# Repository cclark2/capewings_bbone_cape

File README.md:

CapeWings BeagleBone Cape
=========================

Breaks down cape stacks into a form factor easier to debug without having to keep removing capes. Supports selectively jumpering signals between the BeagleBone and up to three capes. Also allows multiple BeagleBones to be connected together. It's a cape developer's dream!

Special thanks to <a href="http://www.sparkfun.com/">SparkFun</a> for use of their open-source EAGLE libraries.

## Project Links
- <a href="http://www.hitchhikeree.org/beaglebone_capes/capewings/">HitchhikerEE page</a>
- <a href="http://www.youtube.com/watch?v=Ci1aKsf_dBM">YouTube video</a>
- <a href="https://docs.google.com/folder/d/0B5HjtPsFD8u5NXZ3VUFZem5UdW8/edit">Design files on Google Drive</a>
- <a href="http://beagleboard.org/CapeContest/entries/CapeWings/">BeagleBone Cape Contest page</a>

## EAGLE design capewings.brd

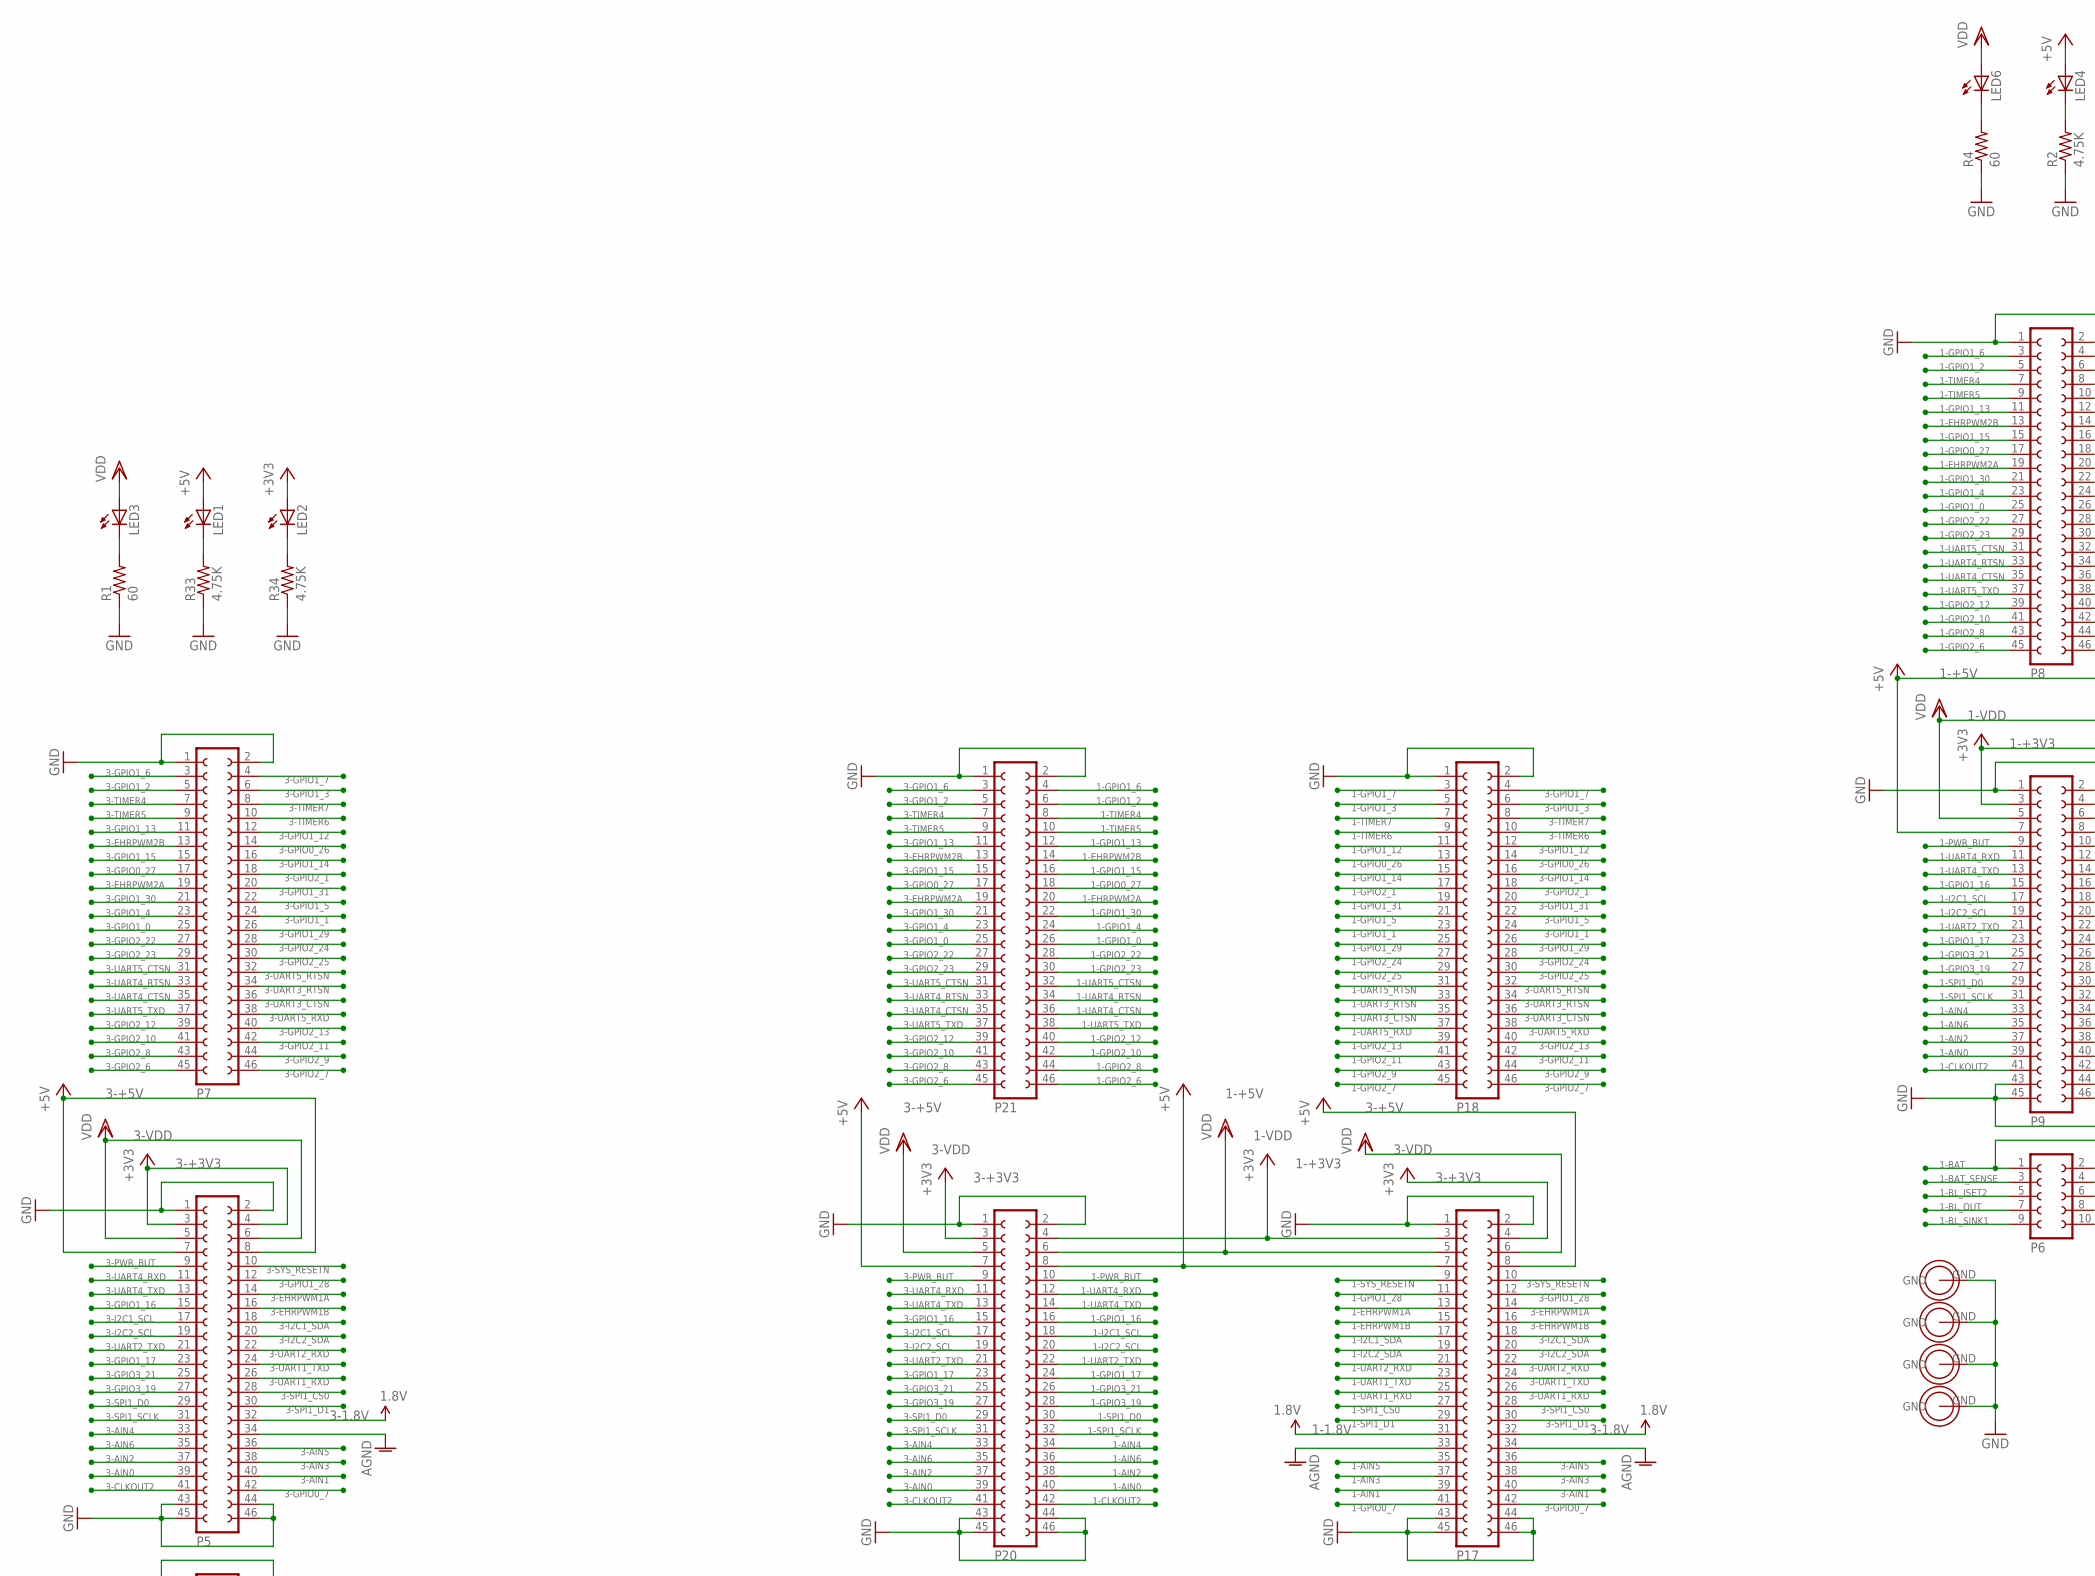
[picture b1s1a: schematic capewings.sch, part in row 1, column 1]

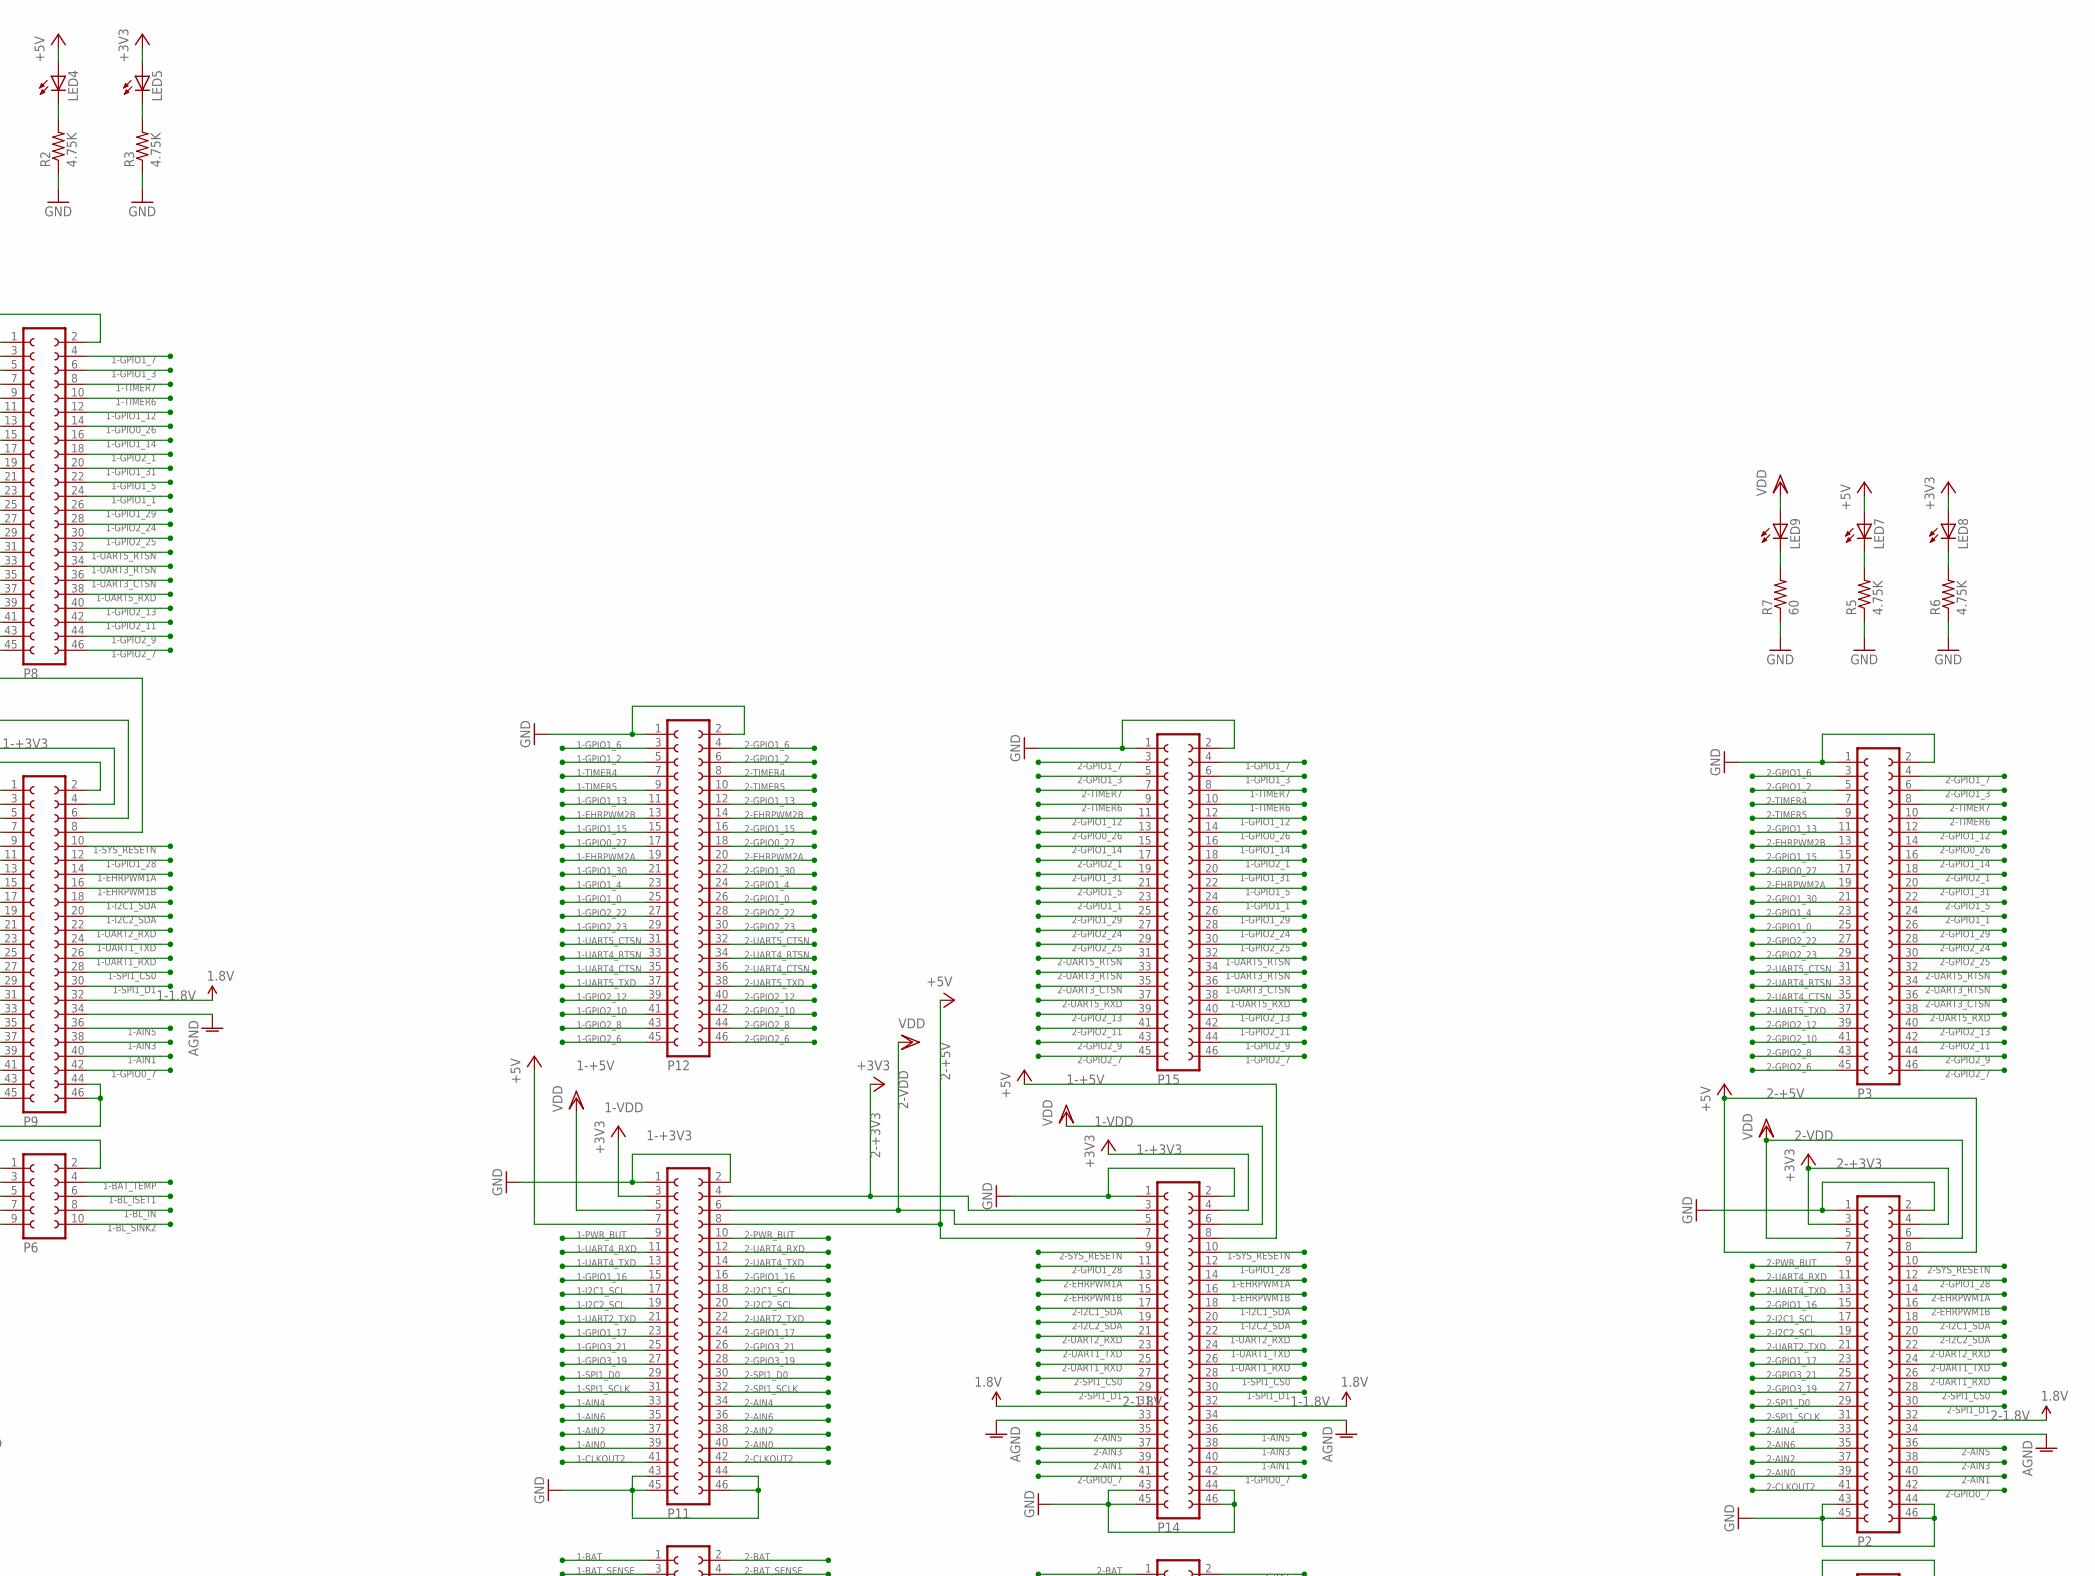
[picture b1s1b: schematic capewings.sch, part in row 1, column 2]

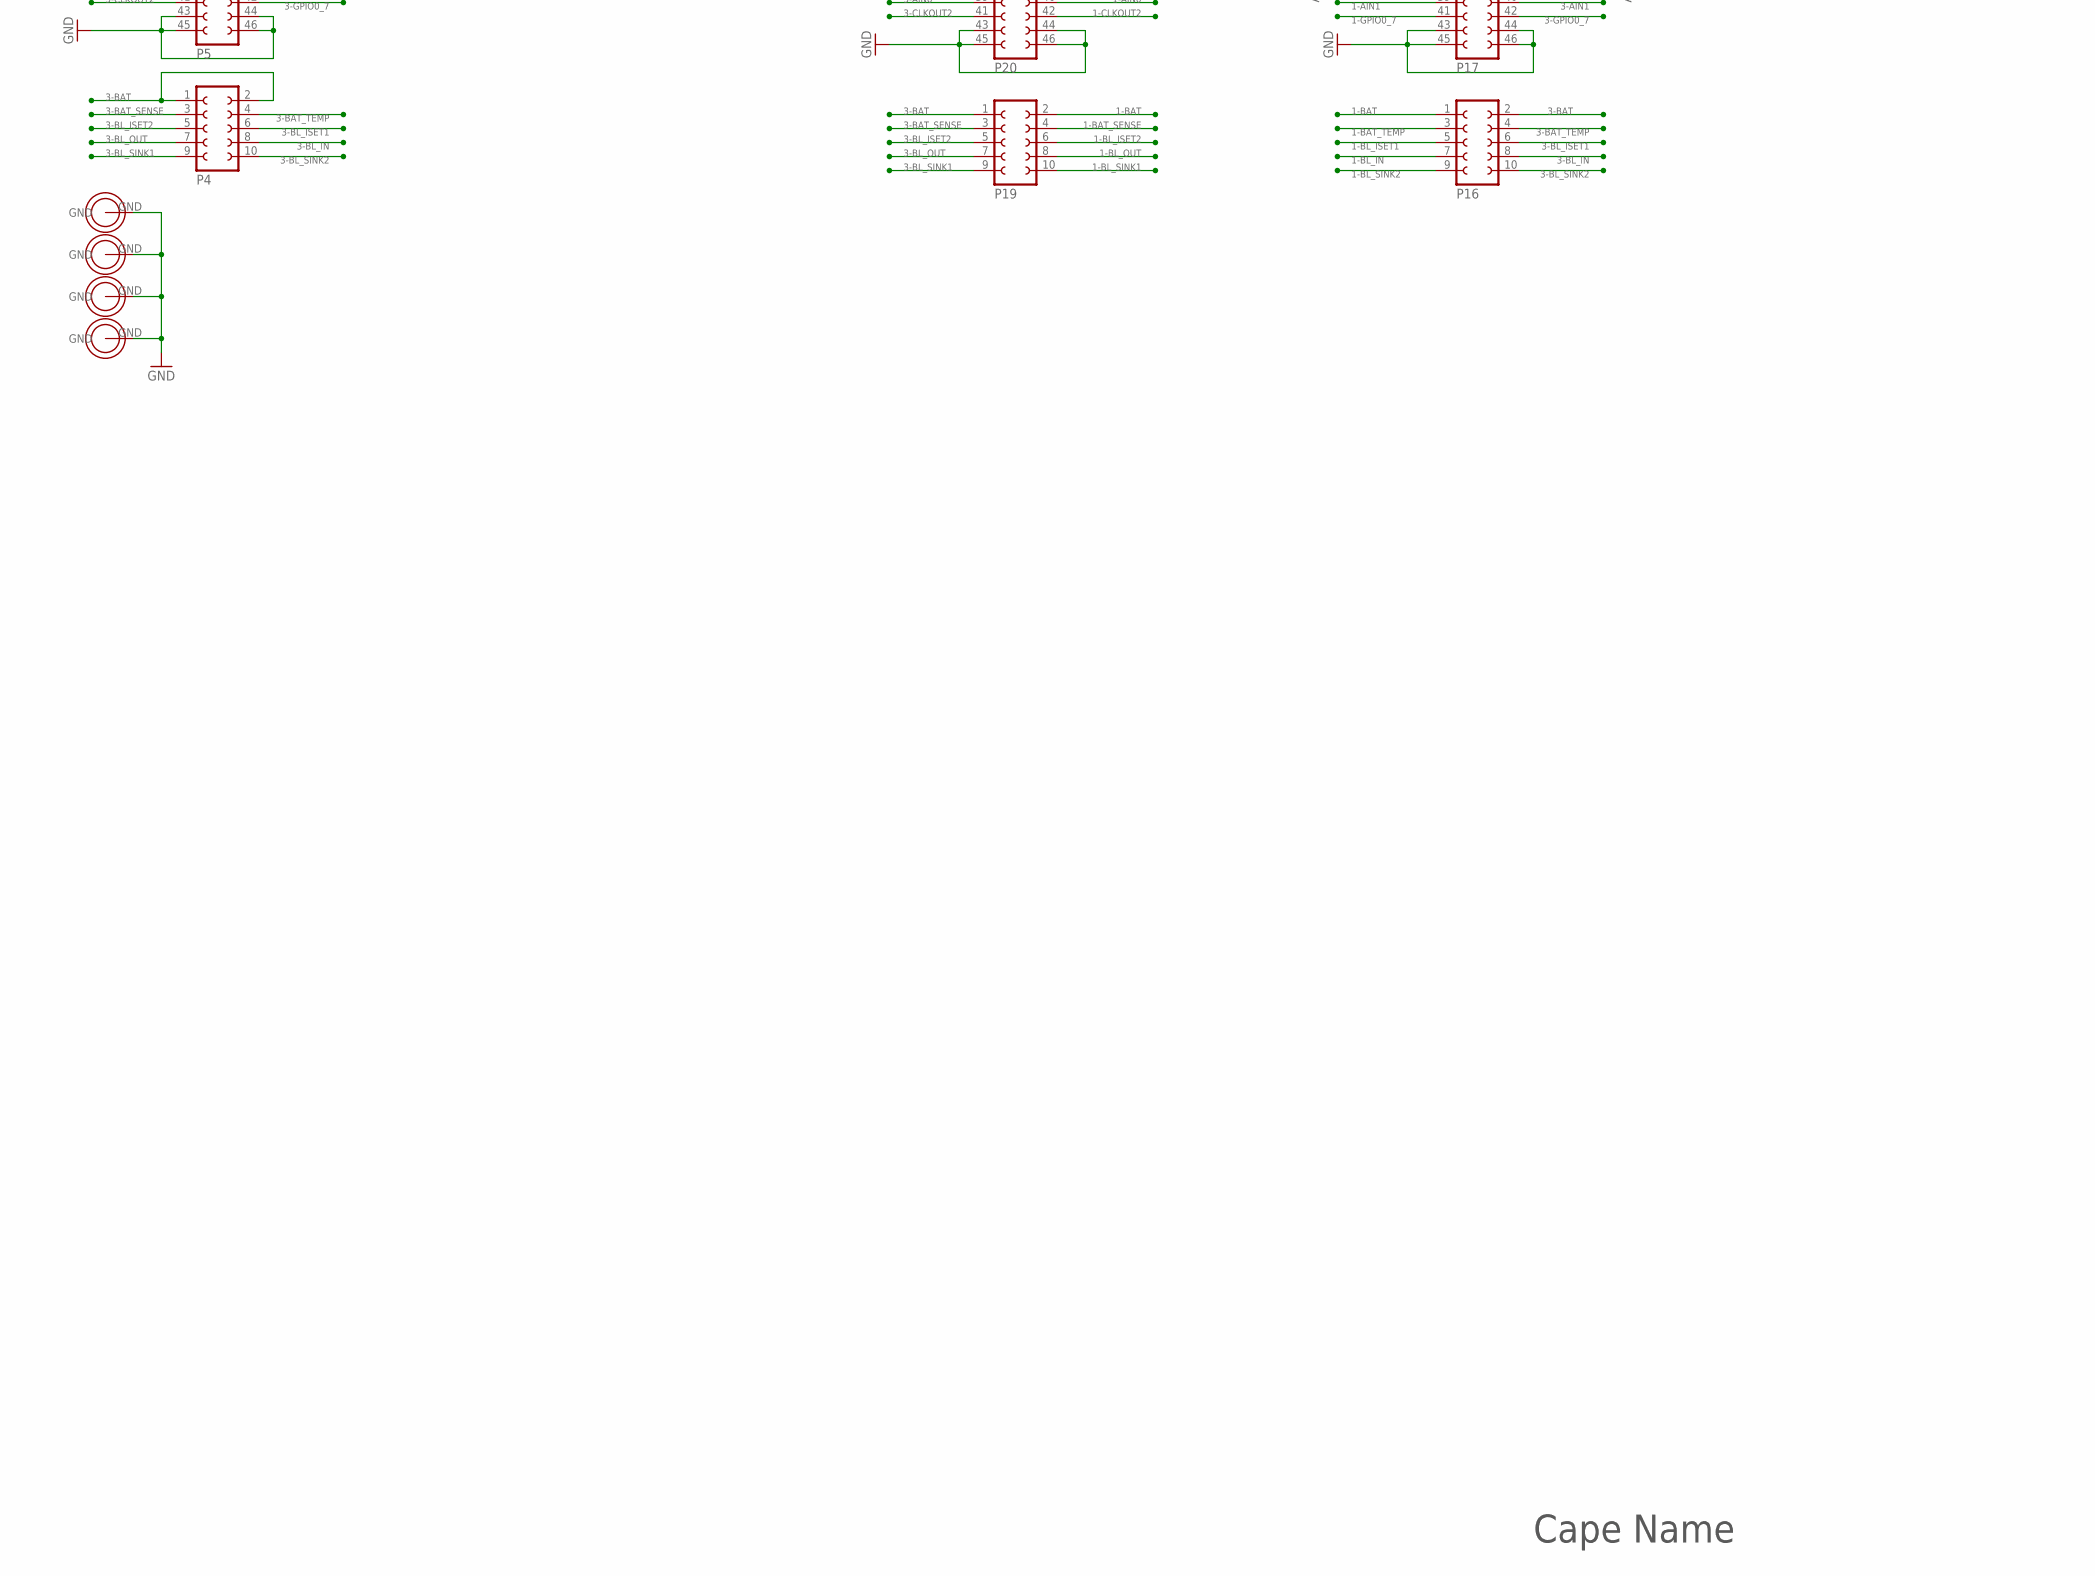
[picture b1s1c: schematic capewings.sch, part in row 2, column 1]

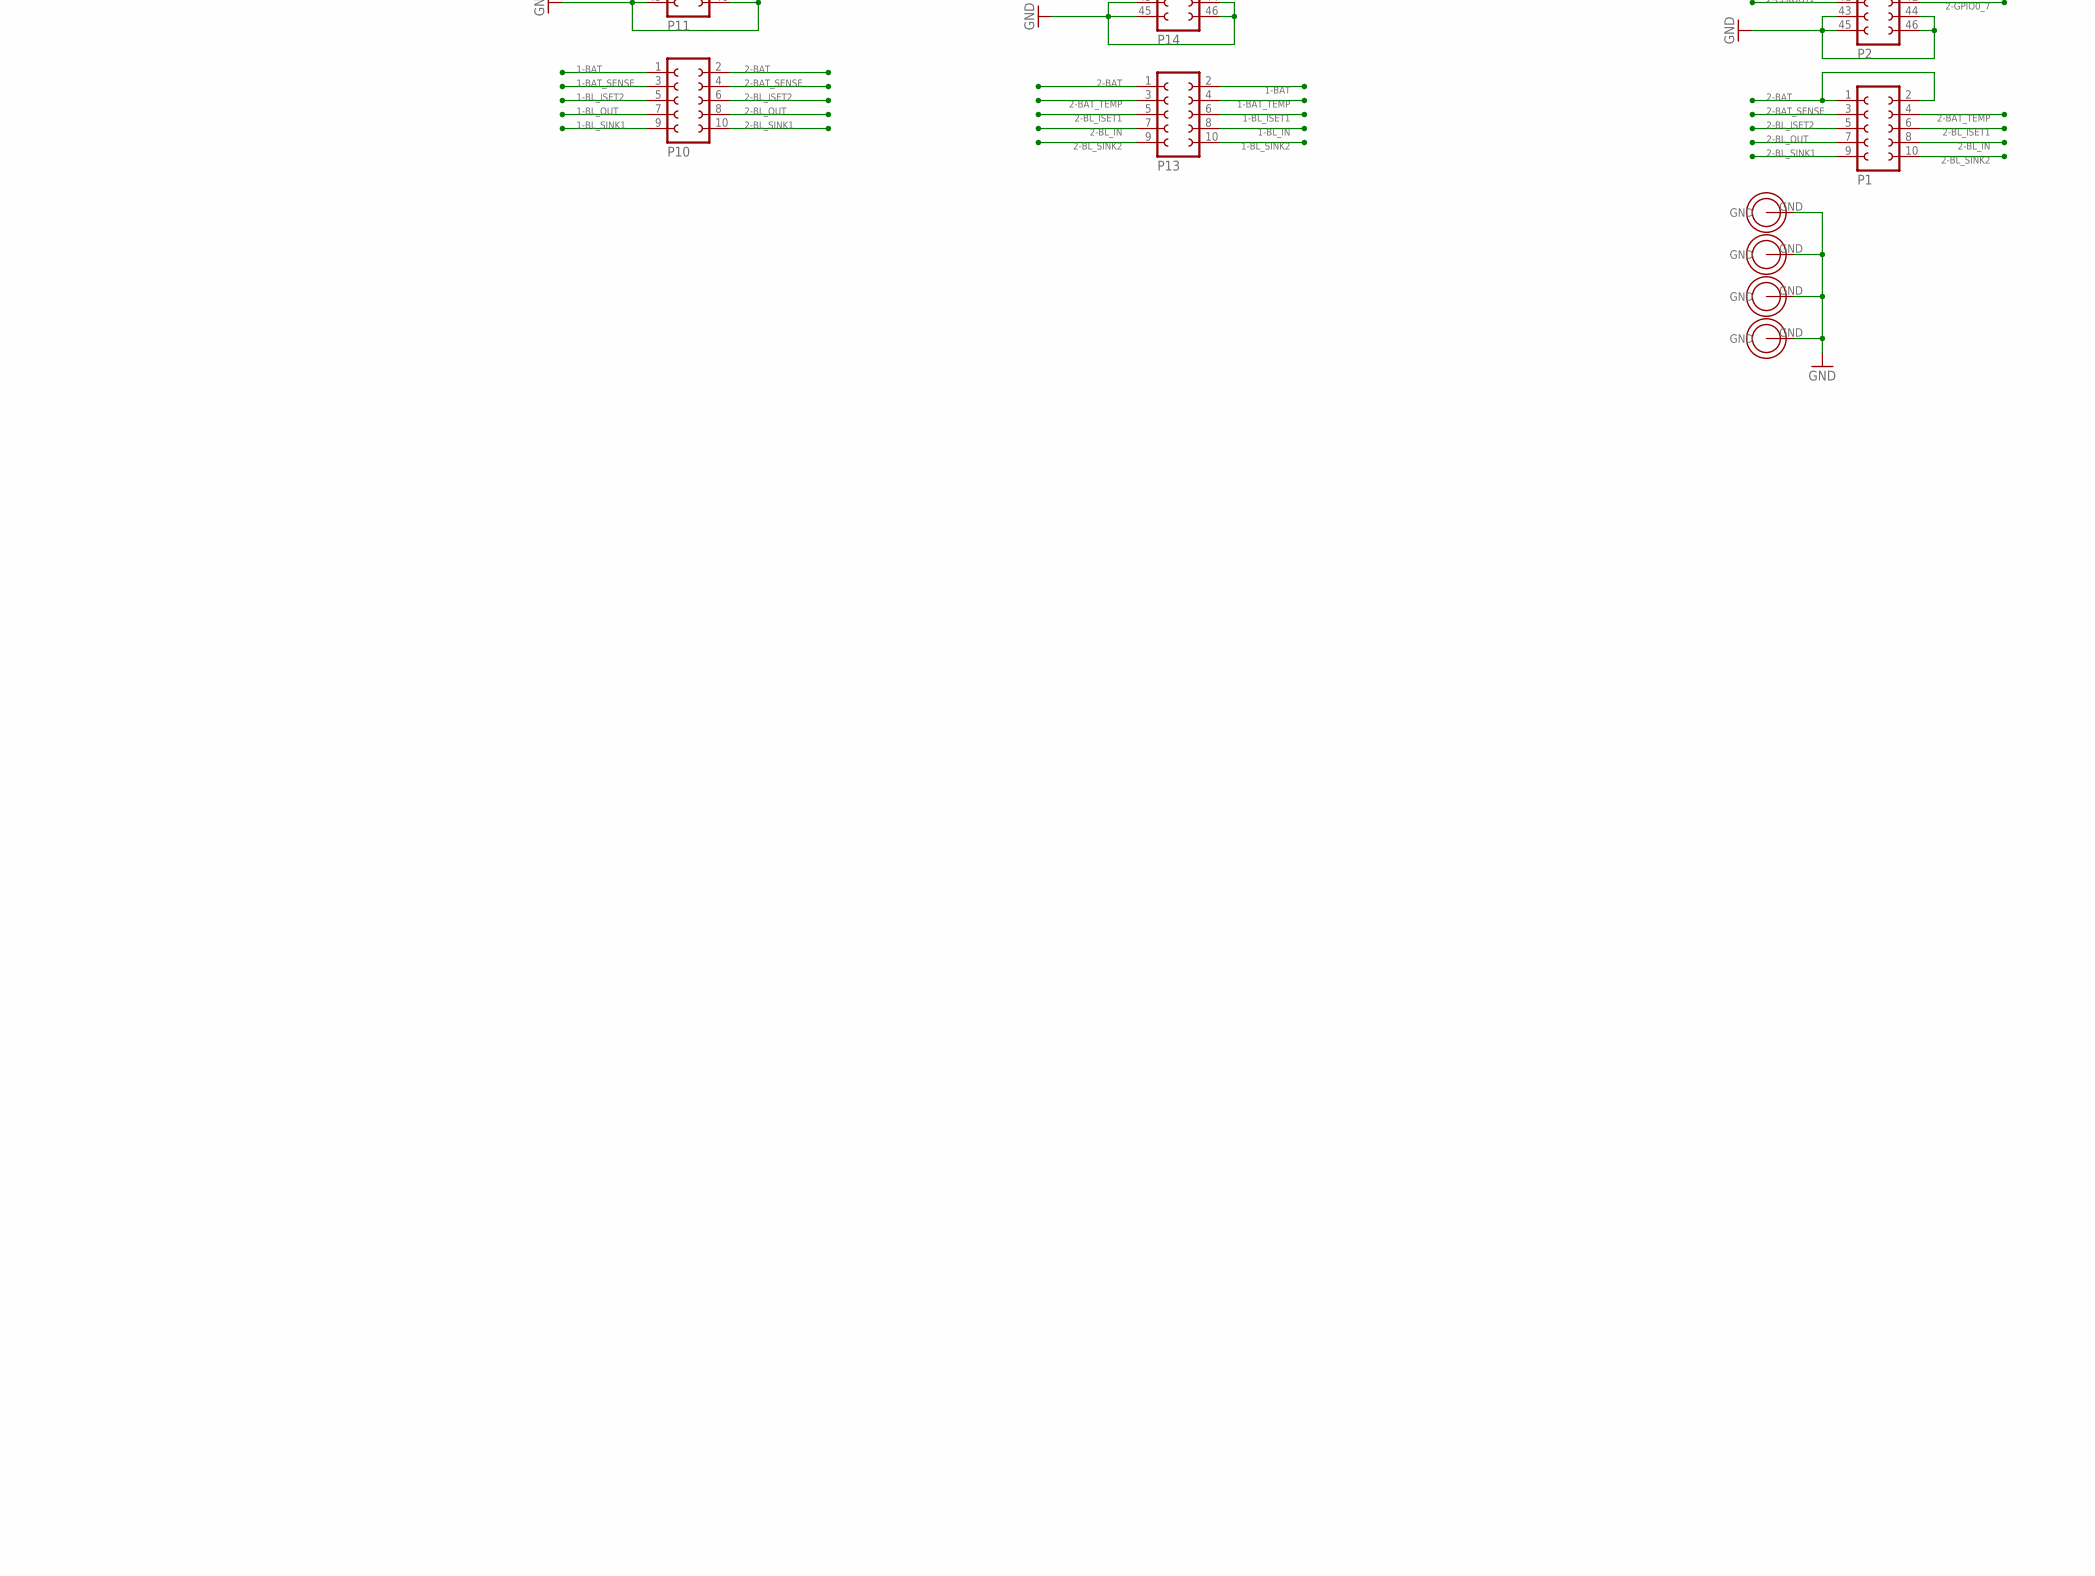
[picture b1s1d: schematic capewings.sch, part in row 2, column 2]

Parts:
H1, H2, H3, H4, H5, H6, H7, H8, H9, H10, H11, H12: HOLE
LED1, LED2, LED3, LED4, LED5, LED6, LED7, LED8, LED9: LEDCHIPLED_0603; CHIPLED_0603
P1, P4, P6, P10, P13, P16, P19: FE05-2
P2, P3, P5, P7, P8, P9, P11, P12, P14, P15, P17, P18, P20, P21: FE23-2
R1, R4: 60; R0603; MPN 302-60.4-RC
R2, R3, R5, R6, R33, R34: 4.75K; R0603
R7: 60; R0603

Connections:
1-1.8V: P9.32, P14.32, P17.31
1-+3V3: LED5.A, P9.3, P9.4, P11.3, P14.4, P17.3, P20.4
1-+5V: LED4.A, P9.7, P9.8, P11.7, P14.8, P17.7, P20.8
1-AIN0: P9.39, P11.39, P20.40
1-AIN1: P9.40, P14.40, P17.39
1-AIN2: P9.37, P11.37, P20.38
1-AIN3: P9.38, P14.38, P17.37
1-AIN4: P9.33, P11.33, P20.34
1-AIN5: P9.36, P14.36, P17.35
1-AIN6: P9.35, P11.35, P20.36
1-BAT: P6.1, P6.2, P10.1, P13.2, P16.1, P19.2
1-BAT_SENSE: P6.3, P10.3, P19.4
1-BAT_TEMP: P6.4, P13.4, P16.3
1-BL_IN: P6.8, P13.8, P16.7
1-BL_ISET1: P6.6, P13.6, P16.5
1-BL_ISET2: P6.5, P10.5, P19.6
1-BL_OUT: P6.7, P10.7, P19.8
1-BL_SINK1: P6.9, P10.9, P19.10
1-BL_SINK2: P6.10, P13.10, P16.9
1-CLKOUT2: P9.41, P11.41, P20.42
1-EHRPWM1A: P9.14, P14.14, P17.13
1-EHRPWM1B: P9.16, P14.16, P17.15
1-EHRPWM2A: P8.19, P12.19, P21.20
1-EHRPWM2B: P8.13, P12.13, P21.14
1-GPIO0_7: P9.42, P14.42, P17.41
1-GPIO0_26: P8.14, P15.14, P18.13
1-GPIO0_27: P8.17, P12.17, P21.18
1-GPIO1_0: P8.25, P12.25, P21.26
1-GPIO1_1: P8.24, P15.24, P18.23
1-GPIO1_2: P8.5, P12.5, P21.6
1-GPIO1_3: P8.6, P15.6, P18.5
1-GPIO1_4: P8.23, P12.23, P21.24
1-GPIO1_5: P8.22, P15.22, P18.21
1-GPIO1_6: P8.3, P12.3, P21.4
1-GPIO1_7: P8.4, P15.4, P18.3
1-GPIO1_12: P8.12, P15.12, P18.11
1-GPIO1_13: P8.11, P12.11, P21.12
1-GPIO1_14: P8.16, P15.16, P18.15
1-GPIO1_15: P8.15, P12.15, P21.16
1-GPIO1_16: P9.15, P11.15, P20.16
1-GPIO1_17: P9.23, P11.23, P20.24
1-GPIO1_28: P9.12, P14.12, P17.11
1-GPIO1_29: P8.26, P15.26, P18.25
1-GPIO1_30: P8.21, P12.21, P21.22
1-GPIO1_31: P8.20, P15.20, P18.19
1-GPIO2_1: P8.18, P15.18, P18.17
1-GPIO2_6: P8.45, P12.45, P21.46
1-GPIO2_7: P8.46, P15.46, P18.45
1-GPIO2_8: P8.43, P12.43, P21.44
1-GPIO2_9: P8.44, P15.44, P18.43
1-GPIO2_10: P8.41, P12.41, P21.42
1-GPIO2_11: P8.42, P15.42, P18.41
1-GPIO2_12: P8.39, P12.39, P21.40
1-GPIO2_13: P8.40, P15.40, P18.39
1-GPIO2_22: P8.27, P12.27, P21.28
1-GPIO2_23: P8.29, P12.29, P21.30
1-GPIO2_24: P8.28, P15.28, P18.27
1-GPIO2_25: P8.30, P15.30, P18.29
1-GPIO3_19: P9.27, P11.27, P20.28
1-GPIO3_21: P9.25, P11.25, P20.26
1-I2C1_SCL: P9.17, P11.17, P20.18
1-I2C1_SDA: P9.18, P14.18, P17.17
1-I2C2_SCL: P9.19, P11.19, P20.20
1-I2C2_SDA: P9.20, P14.20, P17.19
1-PWR_BUT: P9.9, P11.9, P20.10
1-SPI1_CS0: P9.28, P14.28, P17.27
1-SPI1_D0: P9.29, P11.29, P20.30
1-SPI1_D1: P9.30, P14.30, P17.29
1-SPI1_SCLK: P9.31, P11.31, P20.32
1-SYS_RESETN: P9.10, P14.10, P17.9
1-TIMER4: P8.7, P12.7, P21.8
1-TIMER5: P8.9, P12.9, P21.10
1-TIMER6: P8.10, P15.10, P18.9
1-TIMER7: P8.8, P15.8, P18.7
1-UART1_RXD: P9.26, P14.26, P17.25
1-UART1_TXD: P9.24, P14.24, P17.23
1-UART2_RXD: P9.22, P14.22, P17.21
1-UART2_TXD: P9.21, P11.21, P20.22
1-UART3_CTSN: P8.36, P15.36, P18.35
1-UART3_RTSN: P8.34, P15.34, P18.33
1-UART4_CTSN: P8.35, P12.35, P21.36
1-UART4_RTSN: P8.33, P12.33, P21.34
1-UART4_RXD: P9.11, P11.11, P20.12
1-UART4_TXD: P9.13, P11.13, P20.14
1-UART5_CTSN: P8.31, P12.31, P21.32
1-UART5_RTSN: P8.32, P15.32, P18.31
1-UART5_RXD: P8.38, P15.38, P18.37
1-UART5_TXD: P8.37, P12.37, P21.38
1-VDD: LED6.A, P9.5, P9.6, P11.5, P14.6, P17.5, P20.6
2-1.8V: P2.32, P14.31
2-+3V3: LED8.A, P2.3, P2.4, P11.4, P14.3
2-+5V: LED7.A, P2.7, P2.8, P11.8, P14.7
2-AIN0: P2.39, P11.40
2-AIN1: P2.40, P14.39
2-AIN2: P2.37, P11.38
2-AIN3: P2.38, P14.37
2-AIN4: P2.33, P11.34
2-AIN5: P2.36, P14.35
2-AIN6: P2.35, P11.36
2-BAT: P1.1, P1.2, P10.2, P13.1
2-BAT_SENSE: P1.3, P10.4
2-BAT_TEMP: P1.4, P13.3
2-BL_IN: P1.8, P13.7
2-BL_ISET1: P1.6, P13.5
2-BL_ISET2: P1.5, P10.6
2-BL_OUT: P1.7, P10.8
2-BL_SINK1: P1.9, P10.10
2-BL_SINK2: P1.10, P13.9
2-CLKOUT2: P2.41, P11.42
2-EHRPWM1A: P2.14, P14.13
2-EHRPWM1B: P2.16, P14.15
2-EHRPWM2A: P3.19, P12.20
2-EHRPWM2B: P3.13, P12.14
2-GPIO0_7: P2.42, P14.41
2-GPIO0_26: P3.14, P15.13
2-GPIO0_27: P3.17, P12.18
2-GPIO1_0: P3.25, P12.26
2-GPIO1_1: P3.24, P15.23
2-GPIO1_2: P3.5, P12.6
2-GPIO1_3: P3.6, P15.5
2-GPIO1_4: P3.23, P12.24
2-GPIO1_5: P3.22, P15.21
2-GPIO1_6: P3.3, P12.4
2-GPIO1_7: P3.4, P15.3
2-GPIO1_12: P3.12, P15.11
2-GPIO1_13: P3.11, P12.12
2-GPIO1_14: P3.16, P15.15
2-GPIO1_15: P3.15, P12.16
2-GPIO1_16: P2.15, P11.16
2-GPIO1_17: P2.23, P11.24
2-GPIO1_28: P2.12, P14.11
2-GPIO1_29: P3.26, P15.25
2-GPIO1_30: P3.21, P12.22
2-GPIO1_31: P3.20, P15.19
2-GPIO2_1: P3.18, P15.17
2-GPIO2_6: P3.45, P12.46
2-GPIO2_7: P3.46, P15.45
2-GPIO2_8: P3.43, P12.44
2-GPIO2_9: P3.44, P15.43
2-GPIO2_10: P3.41, P12.42
2-GPIO2_11: P3.42, P15.41
2-GPIO2_12: P3.39, P12.40
2-GPIO2_13: P3.40, P15.39
2-GPIO2_22: P3.27, P12.28
2-GPIO2_23: P3.29, P12.30
2-GPIO2_24: P3.28, P15.27
2-GPIO2_25: P3.30, P15.29
2-GPIO3_19: P2.27, P11.28
2-GPIO3_21: P2.25, P11.26
2-I2C1_SCL: P2.17, P11.18
2-I2C1_SDA: P2.18, P14.17
2-I2C2_SCL: P2.19, P11.20
2-I2C2_SDA: P2.20, P14.19
2-PWR_BUT: P2.9, P11.10
2-SPI1_CS0: P2.28, P14.27
2-SPI1_D0: P2.29, P11.30
2-SPI1_D1: P2.30, P14.29
2-SPI1_SCLK: P2.31, P11.32
2-SYS_RESETN: P2.10, P14.9
2-TIMER4: P3.7, P12.8
2-TIMER5: P3.9, P12.10
2-TIMER6: P3.10, P15.9
2-TIMER7: P3.8, P15.7
2-UART1_RXD: P2.26, P14.25
2-UART1_TXD: P2.24, P14.23
2-UART2_RXD: P2.22, P14.21
2-UART2_TXD: P2.21, P11.22
2-UART3_CTSN: P3.36, P15.35
2-UART3_RTSN: P3.34, P15.33
2-UART4_CTSN: P3.35, P12.36
2-UART4_RTSN: P3.33, P12.34
2-UART4_RXD: P2.11, P11.12
2-UART4_TXD: P2.13, P11.14
2-UART5_CTSN: P3.31, P12.32
2-UART5_RTSN: P3.32, P15.31
2-UART5_RXD: P3.38, P15.37
2-UART5_TXD: P3.37, P12.38
2-VDD: LED9.A, P2.5, P2.6, P11.6, P14.5
3-1.8V: P5.32, P17.32
3-+3V3: LED2.A, P5.3, P5.4, P17.4, P20.3
3-+5V: LED1.A, P5.7, P5.8, P17.8, P20.7
3-AIN0: P5.39, P20.39
3-AIN1: P5.40, P17.40
3-AIN2: P5.37, P20.37
3-AIN3: P5.38, P17.38
3-AIN4: P5.33, P20.33
3-AIN5: P5.36, P17.36
3-AIN6: P5.35, P20.35
3-BAT: P4.1, P4.2, P16.2, P19.1
3-BAT_SENSE: P4.3, P19.3
3-BAT_TEMP: P4.4, P16.4
3-BL_IN: P4.8, P16.8
3-BL_ISET1: P4.6, P16.6
3-BL_ISET2: P4.5, P19.5
3-BL_OUT: P4.7, P19.7
3-BL_SINK1: P4.9, P19.9
3-BL_SINK2: P4.10, P16.10
3-CLKOUT2: P5.41, P20.41
3-EHRPWM1A: P5.14, P17.14
3-EHRPWM1B: P5.16, P17.16
3-EHRPWM2A: P7.19, P21.19
3-EHRPWM2B: P7.13, P21.13
3-GPIO0_7: P5.42, P17.42
3-GPIO0_26: P7.14, P18.14
3-GPIO0_27: P7.17, P21.17
3-GPIO1_0: P7.25, P21.25
3-GPIO1_1: P7.24, P18.24
3-GPIO1_2: P7.5, P21.5
3-GPIO1_3: P7.6, P18.6
3-GPIO1_4: P7.23, P21.23
3-GPIO1_5: P7.22, P18.22
3-GPIO1_6: P7.3, P21.3
3-GPIO1_7: P7.4, P18.4
3-GPIO1_12: P7.12, P18.12
3-GPIO1_13: P7.11, P21.11
3-GPIO1_14: P7.16, P18.16
3-GPIO1_15: P7.15, P21.15
3-GPIO1_16: P5.15, P20.15
3-GPIO1_17: P5.23, P20.23
3-GPIO1_28: P5.12, P17.12
3-GPIO1_29: P7.26, P18.26
3-GPIO1_30: P7.21, P21.21
3-GPIO1_31: P7.20, P18.20
3-GPIO2_1: P7.18, P18.18
3-GPIO2_6: P7.45, P21.45
3-GPIO2_7: P7.46, P18.46
3-GPIO2_8: P7.43, P21.43
3-GPIO2_9: P7.44, P18.44
3-GPIO2_10: P7.41, P21.41
3-GPIO2_11: P7.42, P18.42
3-GPIO2_12: P7.39, P21.39
3-GPIO2_13: P7.40, P18.40
3-GPIO2_22: P7.27, P21.27
3-GPIO2_23: P7.29, P21.29
3-GPIO2_24: P7.28, P18.28
3-GPIO2_25: P7.30, P18.30
3-GPIO3_19: P5.27, P20.27
3-GPIO3_21: P5.25, P20.25
3-I2C1_SCL: P5.17, P20.17
3-I2C1_SDA: P5.18, P17.18
3-I2C2_SCL: P5.19, P20.19
3-I2C2_SDA: P5.20, P17.20
3-PWR_BUT: P5.9, P20.9
3-SPI1_CS0: P5.28, P17.28
3-SPI1_D0: P5.29, P20.29
3-SPI1_D1: P5.30, P17.30
3-SPI1_SCLK: P5.31, P20.31
3-SYS_RESETN: P5.10, P17.10
3-TIMER4: P7.7, P21.7
3-TIMER5: P7.9, P21.9
3-TIMER6: P7.10, P18.10
3-TIMER7: P7.8, P18.8
3-UART1_RXD: P5.26, P17.26
3-UART1_TXD: P5.24, P17.24
3-UART2_RXD: P5.22, P17.22
3-UART2_TXD: P5.21, P20.21
3-UART3_CTSN: P7.36, P18.36
3-UART3_RTSN: P7.34, P18.34
3-UART4_CTSN: P7.35, P21.35
3-UART4_RTSN: P7.33, P21.33
3-UART4_RXD: P5.11, P20.11
3-UART4_TXD: P5.13, P20.13
3-UART5_CTSN: P7.31, P21.31
3-UART5_RTSN: P7.32, P18.32
3-UART5_RXD: P7.38, P18.38
3-UART5_TXD: P7.37, P21.37
3-VDD: LED3.A, P5.5, P5.6, P17.6, P20.5
AGND: P2.34, P5.34, P9.34, P14.33, P14.34, P17.33, P17.34
GND: H1.GND, H2.GND, H3.GND, H4.GND, H5.GND, H6.GND, H7.GND, H8.GND, H9.GND, H10.GND, H11.GND, H12.GND, P2.1, P2.2, P2.43, P2.44, P2.45, P2.46, P3.1, P3.2, P5.1, P5.2, P5.43, P5.44, P5.45, P5.46, P7.1, P7.2, P8.1, P8.2, P9.1, P9.2, P9.43, P9.44, P9.45, P9.46, P11.1, P11.2, P11.43, P11.44, P11.45, P11.46, P12.1, P12.2, P14.1, P14.2, P14.43, P14.44, P14.45, P14.46, P15.1, P15.2, P17.1, P17.2, P17.43, P17.44, P17.45, P17.46, P18.1, P18.2, P20.1, P20.2, P20.43, P20.44, P20.45, P20.46, P21.1, P21.2, R1.1, R2.1, R3.1, R4.1, R5.1, R6.1, R7.1, R33.1, R34.1
unnamed: LED3.C, R1.2
unnamed: LED4.C, R2.2
unnamed: LED5.C, R3.2
unnamed: LED6.C, R4.2
unnamed: LED7.C, R5.2
unnamed: LED8.C, R6.2
unnamed: LED9.C, R7.2
unnamed: LED1.C, R33.2
unnamed: LED2.C, R34.2

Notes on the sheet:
Cape Name

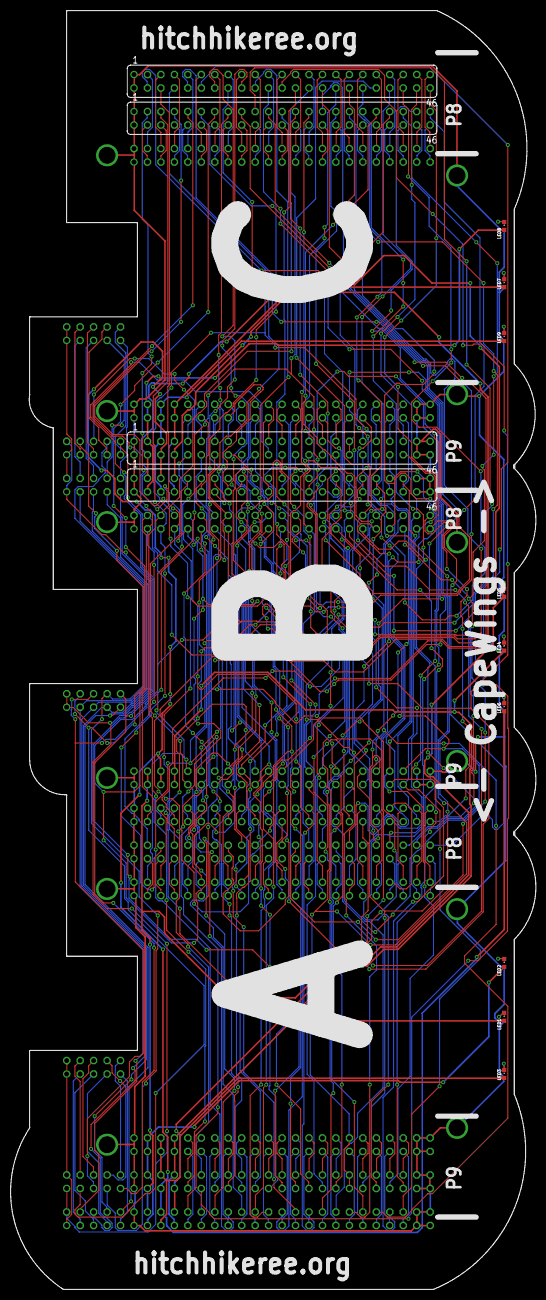
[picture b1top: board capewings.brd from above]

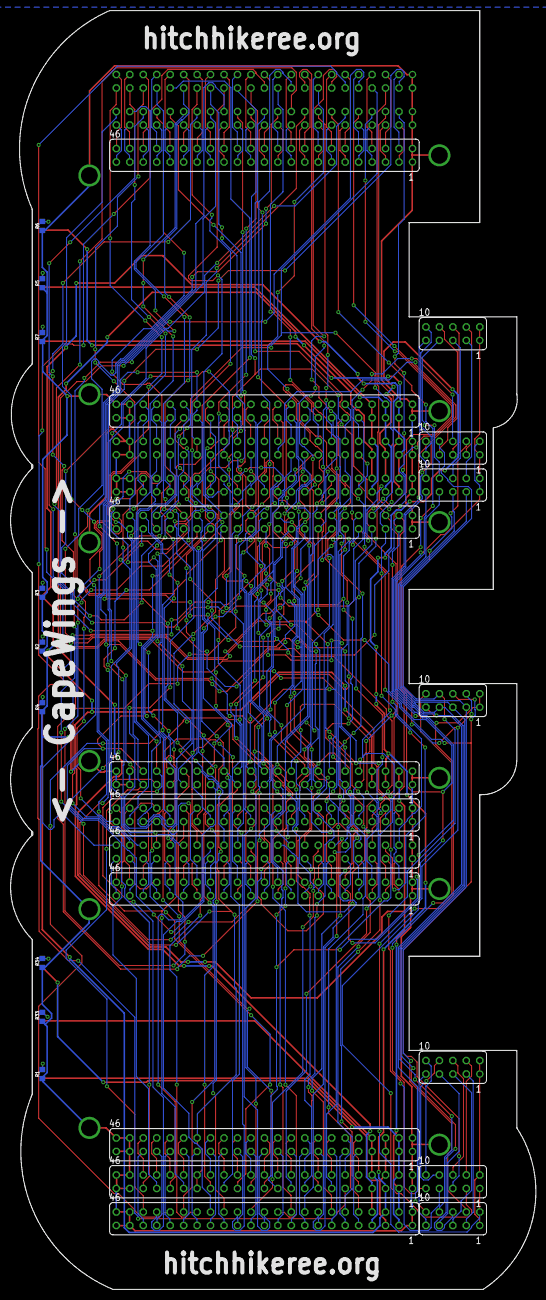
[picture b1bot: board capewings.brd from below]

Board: 2 copper layers, 99.1 x 241.3 mm, 51 parts (26 on the bottom side), 278 nets.

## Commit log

2013-01-01 Design complete, cleanup needed.
2013-01-01 BOM done.
2013-01-06 Added BOM prices, added PDFs of design, sorted files.
2013-01-06 Fixing BOM formatting.
2013-01-06 One last format fix.
2013-01-06 BOM update.
